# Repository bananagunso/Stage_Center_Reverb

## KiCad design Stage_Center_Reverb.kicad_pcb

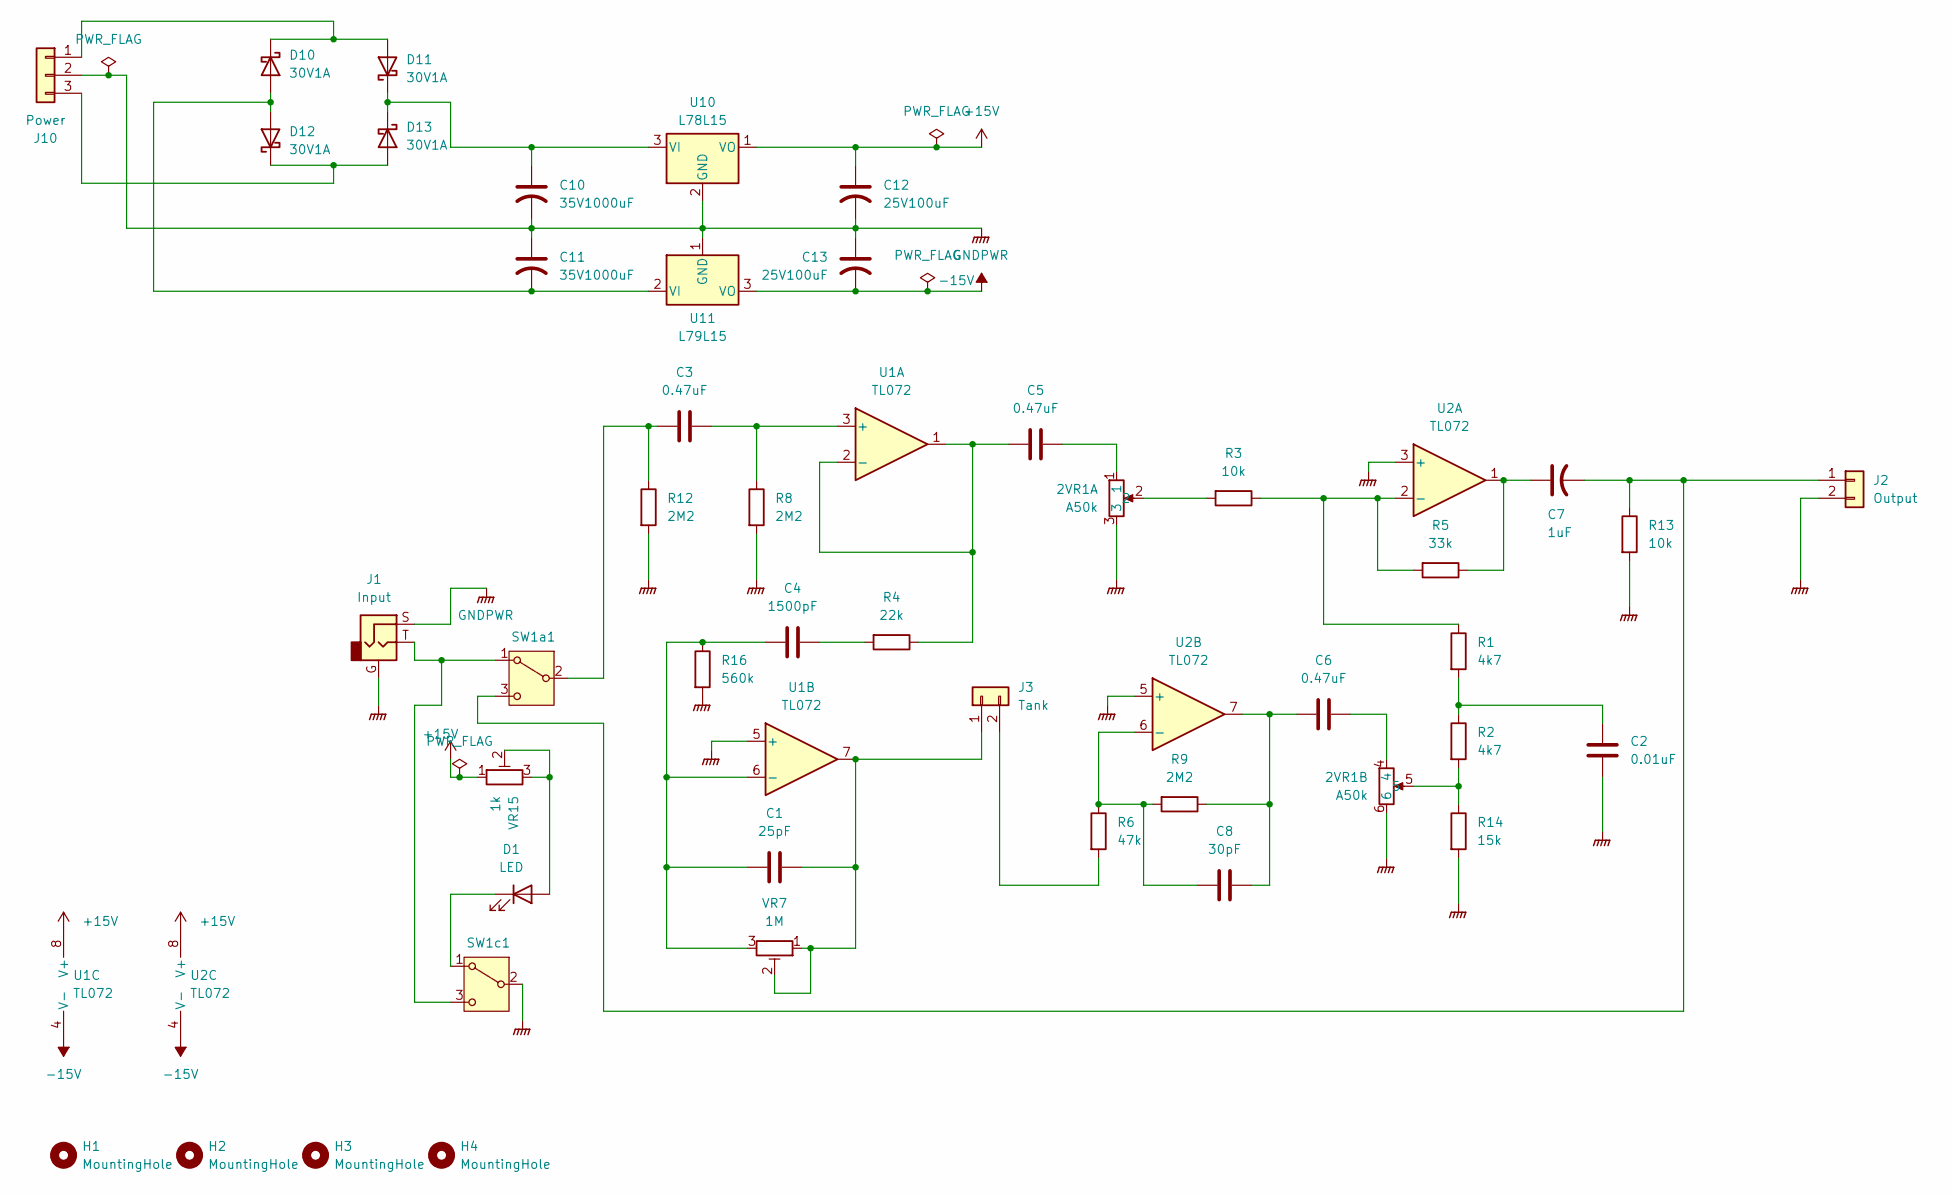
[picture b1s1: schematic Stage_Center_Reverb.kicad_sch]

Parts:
2VR1: A50k; JST_XH_B5B-XH-A_1x05_P2.50mm_Vertical
C1: 25pF; C_Disc_D5.0mm_W2.5mm_P5.00mm
C2: 0.01uF; C_Rect_L7.2mm_W2.5mm_P5.00mm_FKS2_FKP2_MKS2_MKP2
C3, C5, C6: 0.47uF; C_Rect_L7.2mm_W3.5mm_P5.00mm_FKS2_FKP2_MKS2_MKP2
C4: 1500pF; C_Disc_D6.0mm_W2.5mm_P5.00mm
C7: 1uF; C_Rect_L10.3mm_W5.0mm_P7.50mm_MKS4
C8: 30pF; C_Disc_D5.0mm_W2.5mm_P2.50mm
C10, C11: 35V1000uF; CP_Radial_D12.5mm_P5.00mm
C12, C13: 25V100uF; CP_Radial_D7.5mm_P2.50mm
D1: LED
D10, D11, D12, D13: 30V1A; D_DO-41_SOD81_P10.16mm_Horizontal
H1, H2, H3, H4: MountingHole; MountingHole_3.2mm_M3
J1: Input
J2: Output; JST_XH_B2B-XH-A_1x02_P2.50mm_Vertical
J3: Tank; JST_XH_B2B-XH-A_1x02_P2.50mm_Vertical
J10: Power; JST_XH_B3B-XH-A_1x03_P2.50mm_Vertical
R1, R2: 4k7; R_Axial_DIN0207_L6.3mm_D2.5mm_P7.62mm_Horizontal
R3, R13: 10k; R_Axial_DIN0207_L6.3mm_D2.5mm_P7.62mm_Horizontal
R4: 22k; R_Axial_DIN0207_L6.3mm_D2.5mm_P7.62mm_Horizontal
R5: 33k; R_Axial_DIN0207_L6.3mm_D2.5mm_P7.62mm_Horizontal
R6: 47k; R_Axial_DIN0207_L6.3mm_D2.5mm_P7.62mm_Horizontal
R8, R9, R12: 2M2; R_Axial_DIN0207_L6.3mm_D2.5mm_P7.62mm_Horizontal
R14: 15k; R_Axial_DIN0207_L6.3mm_D2.5mm_P7.62mm_Horizontal
R16: 560k; R_Axial_DIN0207_L6.3mm_D2.5mm_P10.16mm_Horizontal
SW1a1, SW1c1: SW_SPDT
U1, U2: TL072; DIP-8_W7.62mm_Socket
U10: L78L15; TO-92_Inline_Wide
U11: L79L15; TO-92_Inline_Wide
VR7: 1M; Potentiometer_Vishay_T73YP_Vertical
VR15: 1k; Potentiometer_Vishay_T73YP_Vertical

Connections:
+15V: C12.1, U1.8 (V+), U2.8 (V+), U10.1 (VO), VR15.1
-15V: C13.2, U1.4 (V-), U2.4 (V-), U11.3 (VO)
GNDPWR: 2VR1.3, 2VR1.6, C2.2, C10.2, C11.1, C12.2, C13.1, J1.G, J1.S, J2.2, J10.2, R8.2, R12.2, R13.2, R14.2, R16.2, SW1c1.2 (B), U1.5 (+), U2.3 (+), U2.5 (+), U10.2 (GND), U11.1 (GND)
unnamed: 2VR1.1, C5.2
unnamed: 2VR1.2, R3.2
unnamed: 2VR1.4, C6.2
unnamed: 2VR1.5, R2.2, R14.1
unnamed: C2.1, R1.2, R2.1
unnamed: C4.2, R4.2
unnamed: C6.1, C8.2, R9.1, U2.7
unnamed: C7.1, R5.1, U2.1
unnamed: D1.2 (A), VR15.2, VR15.3
unnamed: D1.1 (K), SW1c1.1 (A)
unnamed: C11.2, D10.2 (A), D12.2 (A), U11.2 (VI)
unnamed: D10.1 (K), D11.2 (A), J10.1
unnamed: C10.1, D11.1 (K), D13.1 (K), U10.3 (VI)
unnamed: D12.1 (K), D13.2 (A), J10.3
unnamed: J1.T, SW1a1.1 (A), SW1c1.3 (C)
unnamed: C7.2, J2.1, R13.1, SW1a1.3 (C)
unnamed: C1.2, J3.1, U1.7, VR7.1, VR7.2
unnamed: J3.2, R6.2
unnamed: C3.1, R12.1, SW1a1.2 (B)
unnamed: C3.2, R8.1, U1.3 (+)
unnamed: C5.1, R4.1, U1.1, U1.2 (-)
unnamed: C1.1, C4.1, R16.1, U1.6 (-), VR7.3
unnamed: R1.1, R3.1, R5.2, U2.2 (-)
unnamed: C8.1, R6.1, R9.2, U2.6 (-)

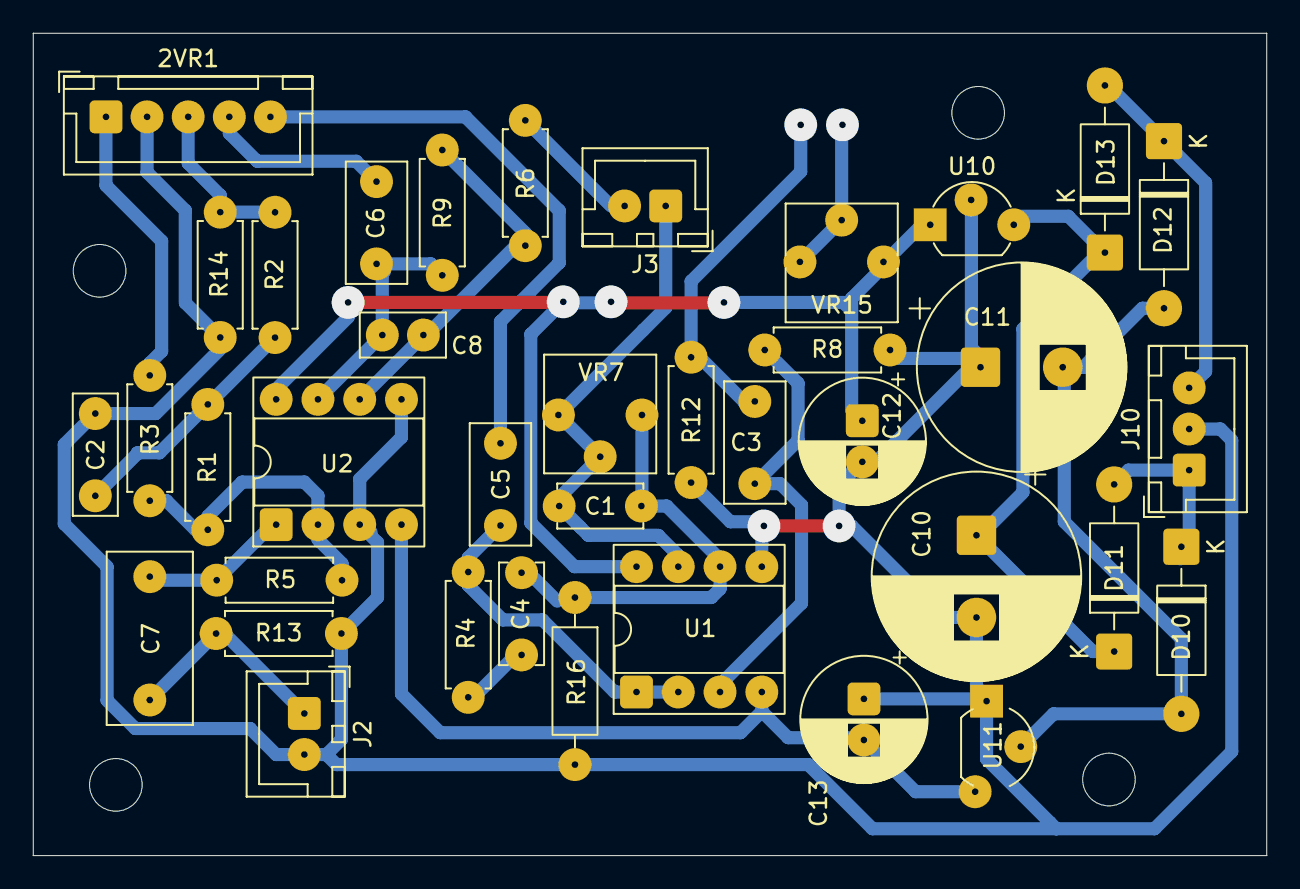
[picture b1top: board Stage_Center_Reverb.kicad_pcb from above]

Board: 2 copper layers, 75.0 x 50.0 mm, 42 parts (0 on the bottom side), 25 nets.

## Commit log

2025-10-24 Initial
2025-10-26 電源部分を変更
2025-10-26 パーツを小型化したフットプリント
2025-10-26 フットプリント修正、LEDの抵抗を可変に変更
2025-10-26 電源をトランスから正負15Vを作るように変更 コネクタ等との接続をXHコネクタを使うよう変更
2025-10-27 エッチングのため配線が狭いところを修正
2025-10-28 電元部分の電解コンデンサを35Vに変更 ICを抜きやすいよう配置を修正
2025-10-28 LED周りの修正
2025-10-29 配置換えしたときにGNDの接続が抜けていた
2025-10-30 回路図上トゥルーバイパスがグランドに落ちていたのを修正
2025-10-31 C4,R6のハイパスフィルタのカットオフ周波数をを下げた
2025-11-02 ICまわりの配置を修正
2025-11-02 ベタをハッチパターンにした
2025-11-03 線が近いところを修正、ハッチングを45°に変更してみた
2025-11-03 GNDはベタだけにする
2025-11-03 GNDベタ禁止エリアを追加
2025-11-03 配線を修正
2025-11-03 配置を修正
2025-11-09 全体ではなく外周をGNDで囲むように変更
2025-11-09 ラインを0.4、パッドやビアを直径 2 2、ドリル穴を0.4に
2025-11-10 パッドの大きさとドリル穴を2に変更
2025-11-10 配線を0.6にして修正
2025-11-12 配線を修正、幅は0.8に。この回路で一旦完成。
